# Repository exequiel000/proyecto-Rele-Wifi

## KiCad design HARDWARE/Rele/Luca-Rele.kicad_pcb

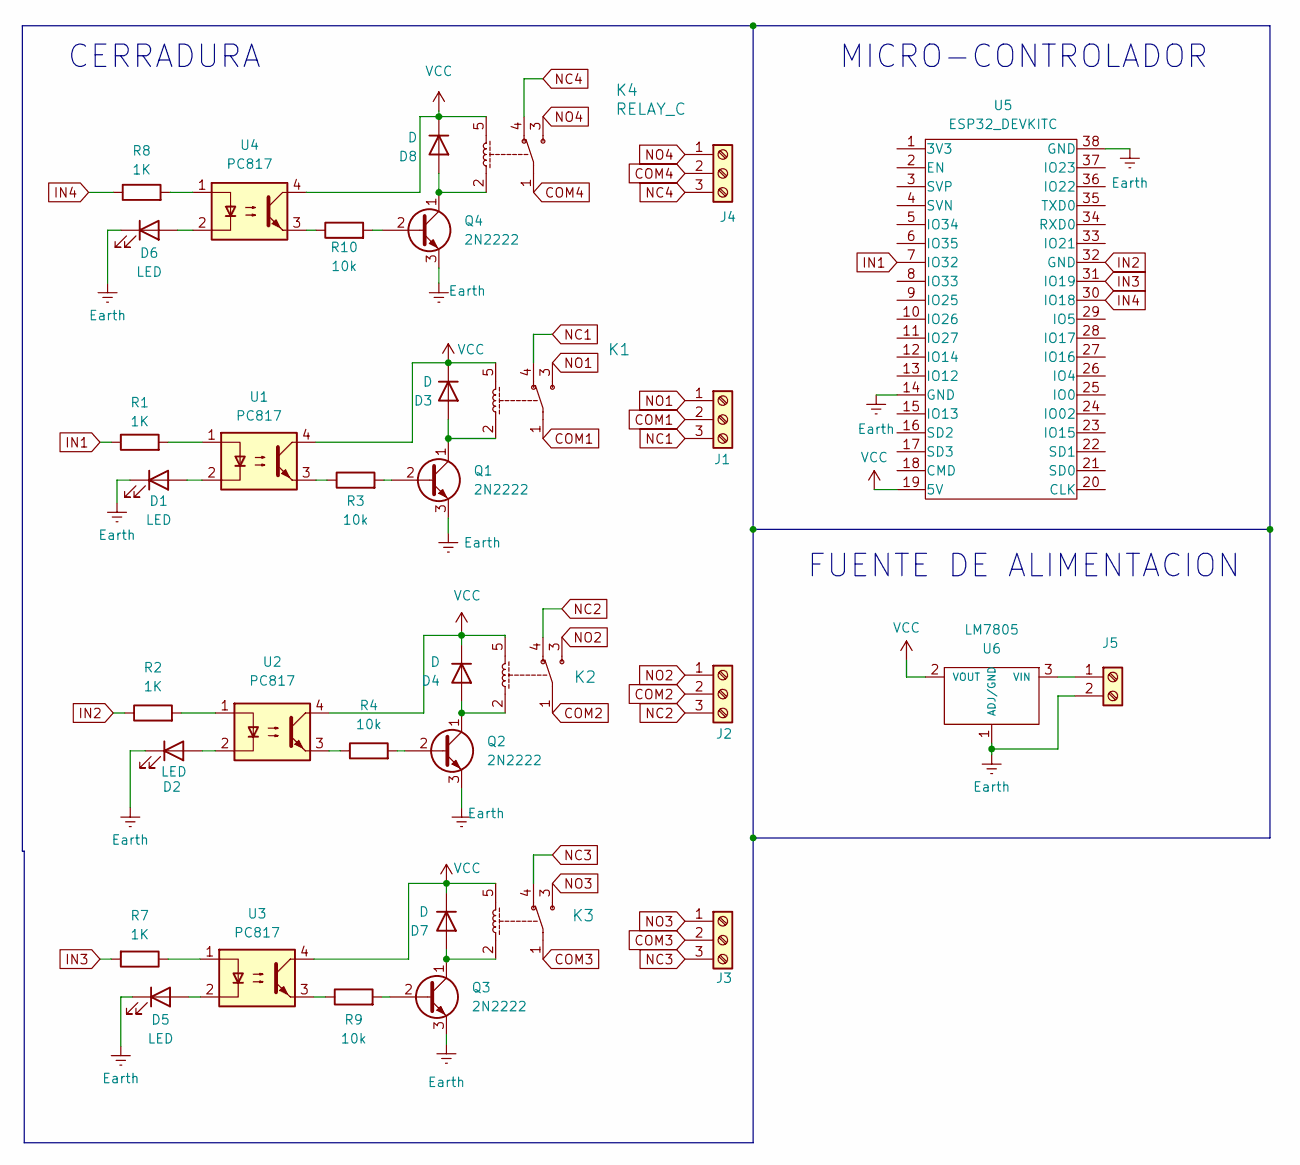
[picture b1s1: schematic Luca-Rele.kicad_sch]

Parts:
D1, D2, D5, D6: LED; LED_0805_2012Metric
D3, D4, D7, D8: D; D_SMA
J1, J2, J3: Screw_Terminal_01x03; TerminalBlock_Xinya_XY308-2.54-3P_1x03_P2.54mm_Horizontal
J4: CERRADURA; TerminalBlock_Xinya_XY308-2.54-3P_1x03_P2.54mm_Horizontal
J5: Screw_Terminal_01x02; TerminalBlock_Xinya_XY308-2.54-2P_1x02_P2.54mm_Horizontal
K1, K2, K3, K4: RELAY_C; Relay_C
Q1, Q2, Q3, Q4: 2N2222; SOT-23
R1, R2, R7, R8: 1K; R_0805_2012Metric
R3, R4, R9, R10: 10k; R_0805_2012Metric
U1, U2, U3, U4: PC817; DIP-4_W7.62mm
U5: ESP32_DEVKITC
U6: LM7805; ATPAK-2

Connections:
COM1: J1.2, K1.1
COM2: J2.2, K2.1
COM3: J3.2, K3.1
COM4: J4.2, K4.1
Earth: D1.1 (K), D2.1 (K), D5.1 (K), D6.1 (K), J5.2, Q1.3 (E), Q2.3 (E), Q3.3 (E), Q4.3 (E), U5.14 (GND), U5.38 (GND), U6.1 (ADJ/GND)
IN1: R1.1, U5.7 (IO32)
IN2: R2.1, U5.32 (GND)
IN3: R7.2, U5.31 (IO19)
IN4: R8.1, U5.30 (IO18)
NC1: J1.3, K1.4
NC2: J2.3, K2.4
NC3: J3.3, K3.4
NC4: J4.3, K4.4
NO1: J1.1, K1.3
NO2: J2.1, K2.3
NO3: J3.1, K3.3
NO4: J4.1, K4.3
unnamed: D1.2 (A), U1.2
unnamed: D2.2 (A), U2.2
unnamed: D3.2 (A), K1.2, Q1.1 (C)
unnamed: D4.2 (A), K2.2, Q2.1 (C)
unnamed: D5.2 (A), U3.2
unnamed: D6.2 (A), U4.2
unnamed: D7.2 (A), K3.2, Q3.1 (C)
unnamed: D8.2 (A), K4.2, Q4.1 (C)
unnamed: J5.1, U6.3 (VIN)
unnamed: Q1.2 (B), R3.2
unnamed: Q2.2 (B), R4.2
unnamed: Q3.2 (B), R9.2
unnamed: Q4.2 (B), R10.2
unnamed: R1.2, U1.1
unnamed: R2.2, U2.1
unnamed: R3.1, U1.3
unnamed: R4.1, U2.3
unnamed: R7.1, U3.1
unnamed: R8.2, U4.1
unnamed: R9.1, U3.3
unnamed: R10.1, U4.3
VCC: D3.1 (K), D4.1 (K), D7.1 (K), D8.1 (K), K1.5, K2.5, K3.5, K4.5, U1.4, U2.4, U3.4, U4.4, U5.19 (5V), U6.2 (VOUT)

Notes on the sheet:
CERRADURA
FUENTE DE ALIMENTACION
MICRO-CONTROLADOR

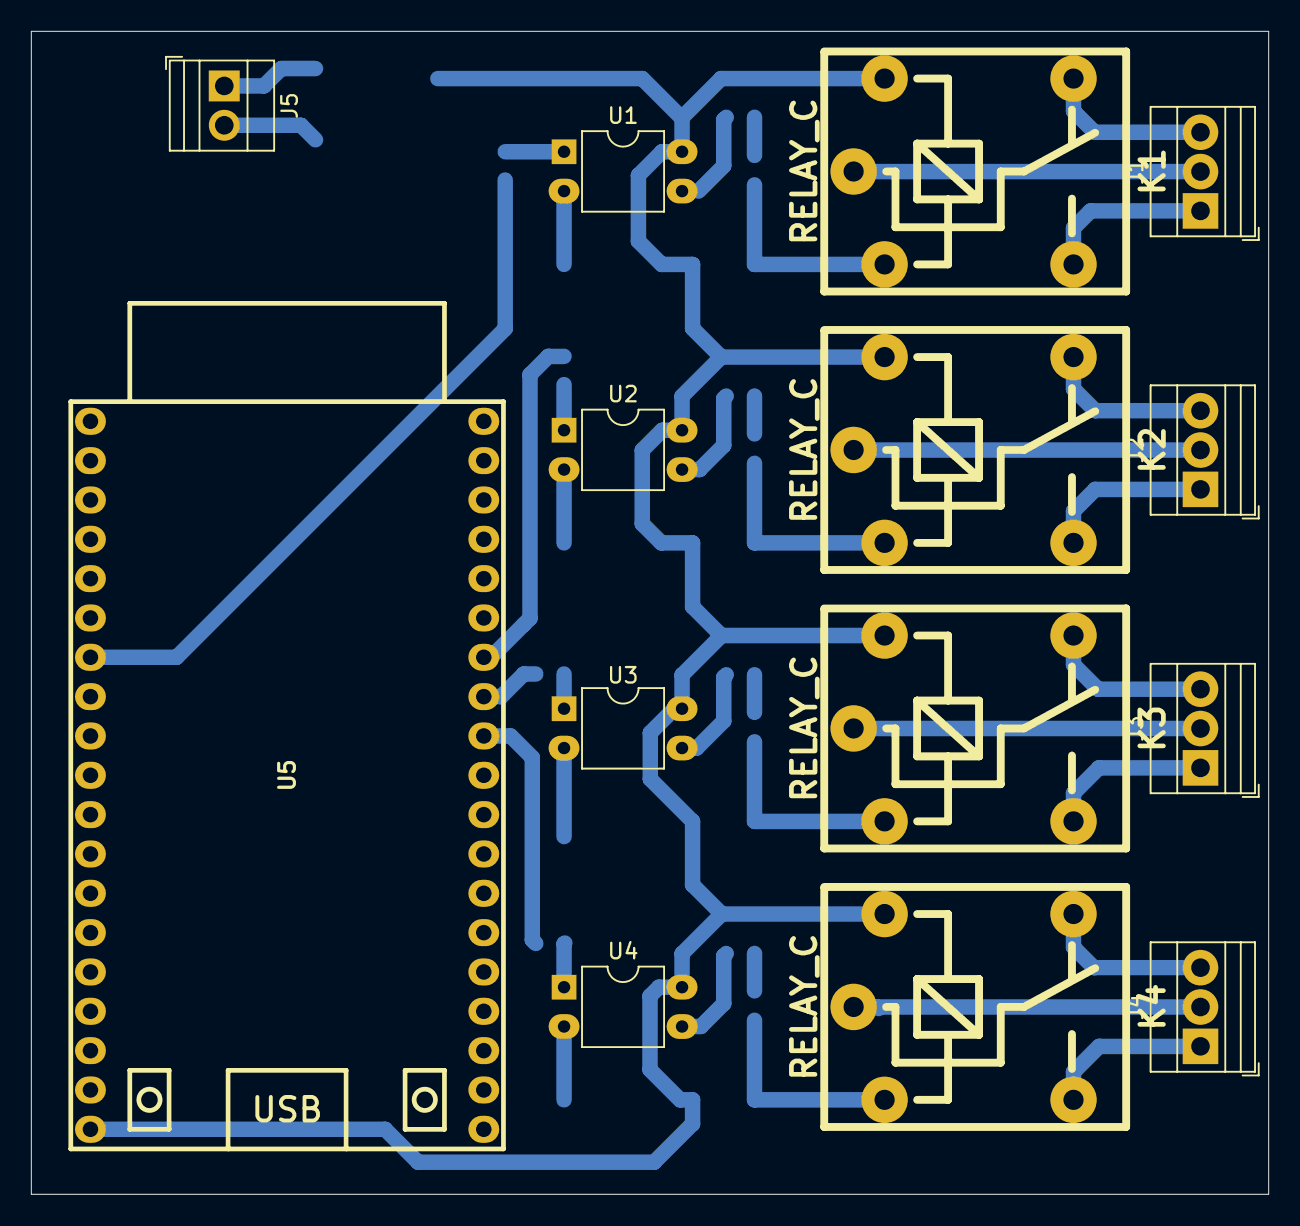
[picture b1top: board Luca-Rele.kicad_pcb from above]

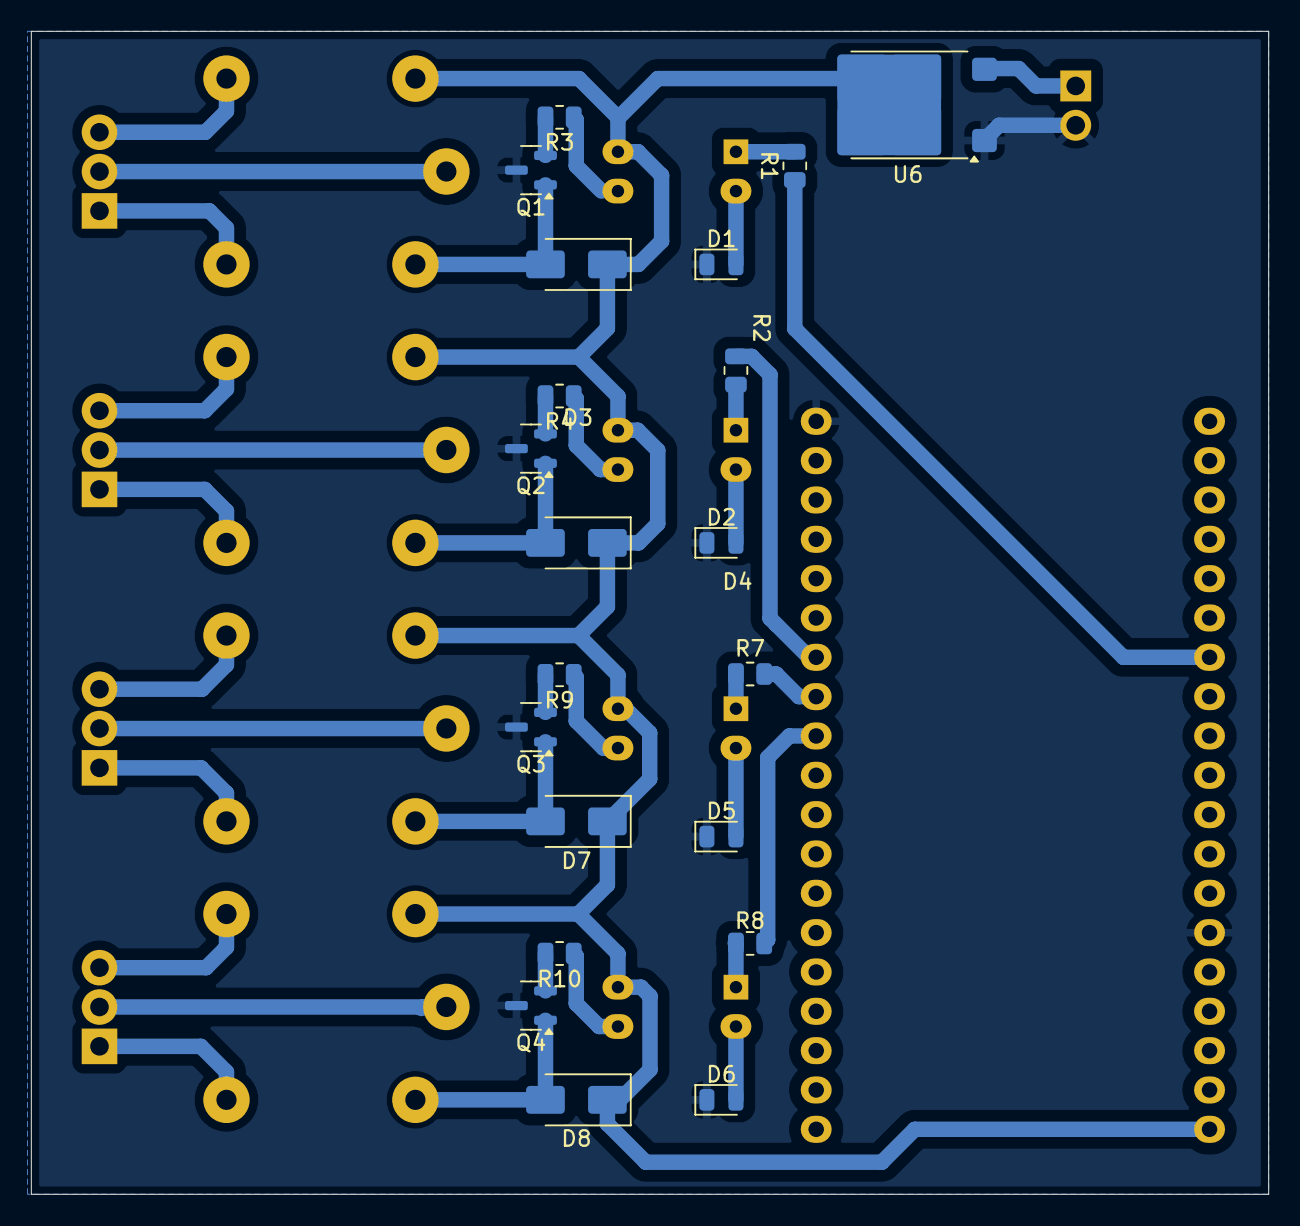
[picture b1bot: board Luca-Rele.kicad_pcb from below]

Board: 2 copper layers, 79.9 x 75.1 mm, 35 parts (21 on the bottom side), 39 nets.

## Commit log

2025-05-20 proyecto-Rele-Widi
2025-05-20 proyecto-Rele-Wifi
